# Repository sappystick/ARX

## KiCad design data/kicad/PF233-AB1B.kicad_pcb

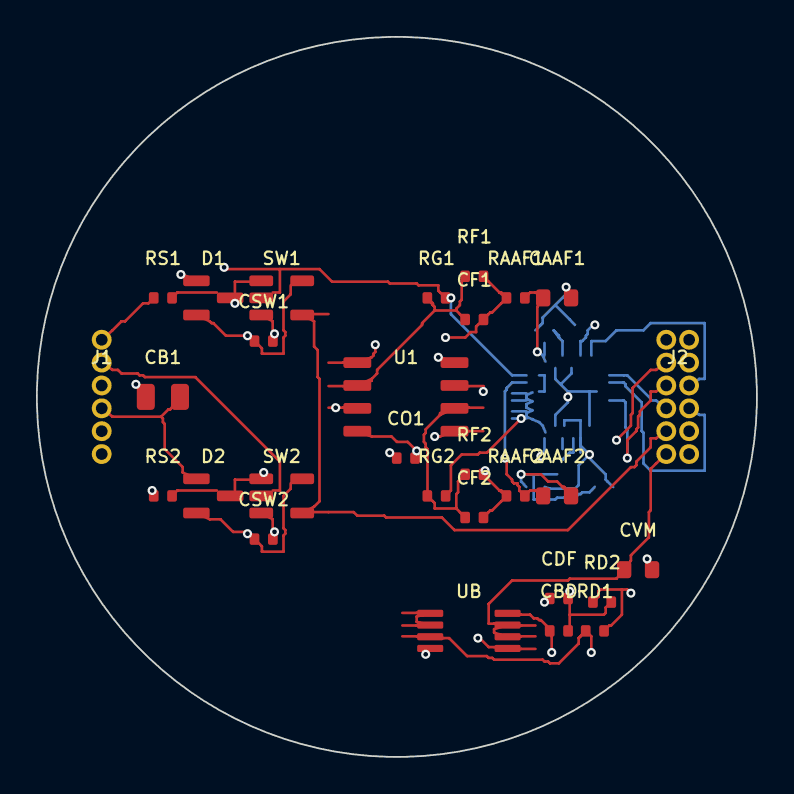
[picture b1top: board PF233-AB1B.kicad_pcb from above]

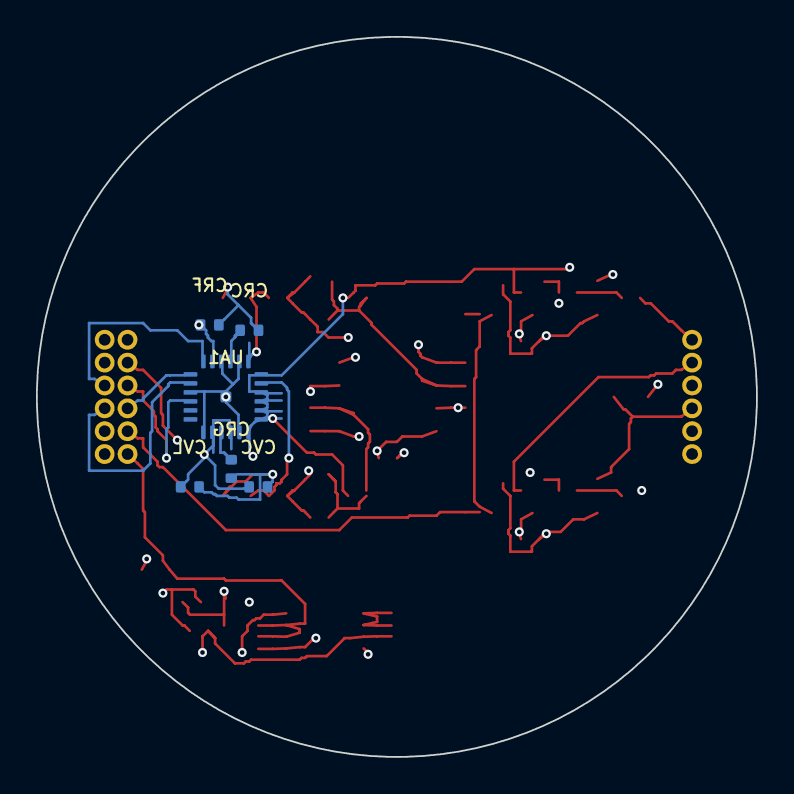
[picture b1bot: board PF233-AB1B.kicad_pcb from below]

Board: 6 copper layers, 40.0 x 40.0 mm, 35 parts (6 on the bottom side), 24 nets.

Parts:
CAAF1, CAAF2: 2n2; C_0603_1608Metric
CB1: 10u; C_0805_2012Metric
CBD: 100n; C_0402_1005Metric
CDF: 100n; C_0402_1005Metric
CF1, CF2: 22p; C_0402_1005Metric
CO1: 100n; C_0402_1005Metric
CRC: 100n; C_0402_1005Metric
CRF: 1u; C_0402_1005Metric
CRG: 1u; C_0402_1005Metric
CSW1, CSW2: 100n; C_0402_1005Metric
CVC: 1u; C_0402_1005Metric
CVL: 1u; C_0402_1005Metric
CVM: 1u; C_0603_1608Metric
D1, D2: BAV199; SOT-23
J1: Antenna harness 6p solder pads 1.27mm; PinHeader_1x6_P1.27mm
J2: Main-board 2x6 1.27mm header; PinHeader_2x6_P1.27mm
RAAF1, RAAF2: 200; R_0402_1005Metric
RD1, RD2: 100k; R_0402_1005Metric
RF1, RF2: 390; R_0402_1005Metric
RG1, RG2: 10; R_0402_1005Metric
RS1, RS2: 1000; R_0402_1005Metric
SW1, SW2: 74LVC1G66; SOT-23-5
U1: OPA2211; SOIC-8_3.9x4.9mm_P1.27mm
UA1: AD7389-4; CP-24-25_ADI_LFCSP-24-1EP_4x4mm_P0.5mm_EP0.61x0.61mm
UB: OPA2365; MSOP-8_3x3mm_P0.65mm

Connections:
+3V3D: CVC.1, CVL.1, J2.3, UA1.2, UA1.4
+5VA: CB1.1, CBD.1, CO1.1, CSW1.1, CSW2.1, D1.2, D2.2, J2.1, SW1.5, SW2.5, U1.8, UB.8
ADCIN_MONO: CAAF2.1, RAAF2.2, UA1.11
ADCIN_Y8: CAAF1.1, RAAF1.2, UA1.13
BLANK: J2.9, SW1.4, SW2.4
CS: J2.6, UA1.18
FB_MONO: CF2.1, RF2.1, RG2.1, U1.6
FB_Y8: CF1.1, RF1.1, RG1.1, U1.2
GND: CAAF1.2, CAAF2.2, CB1.2, CBD.2, CDF.2, CO1.2, CRC.2, CRF.2, CRG.2, CSW1.2, CSW2.2, CVC.2, CVL.2, CVM.2, D1.1, D2.1, J1.3, J1.4, J1.5, J1.6, J2.2, J2.4, J2.12, RD2.2, SW1.3, SW2.3, U1.4, UA1.1, UA1.5, UA1.14, UA1.16, UA1.21, UA1.25, UB.4
IN_MONO: D2.3, RS2.2, SW2.1, U1.5
IN_Y8: D1.3, RS1.2, SW1.1, U1.3
OUT_MONO: CF2.2, RAAF2.1, RF2.2, U1.7
OUT_Y8: CF1.2, RAAF1.1, RF1.2, U1.1
RAW_MONO: J2.10, RS2.1
RAW_Y8: J1.1, RS1.1
REFCAP: CRC.1, UA1.15
REGCAP: CRG.1, UA1.3
SCLK: J2.5, UA1.22
SDO1: J2.7, UA1.19
SDO2: J2.8, UA1.20
VCM: CVM.1, J1.2, J2.11, RG1.2, RG2.2, SW1.2, SW2.2, UA1.6, UA1.7, UA1.8, UA1.9, UA1.10, UA1.12, UB.6, UB.7
VCM_DIV: CDF.1, RD1.2, RD2.1, UB.5
VREF: UB.1, UB.2
VREF_RAW: CRF.1, RD1.1, UA1.17, UB.3

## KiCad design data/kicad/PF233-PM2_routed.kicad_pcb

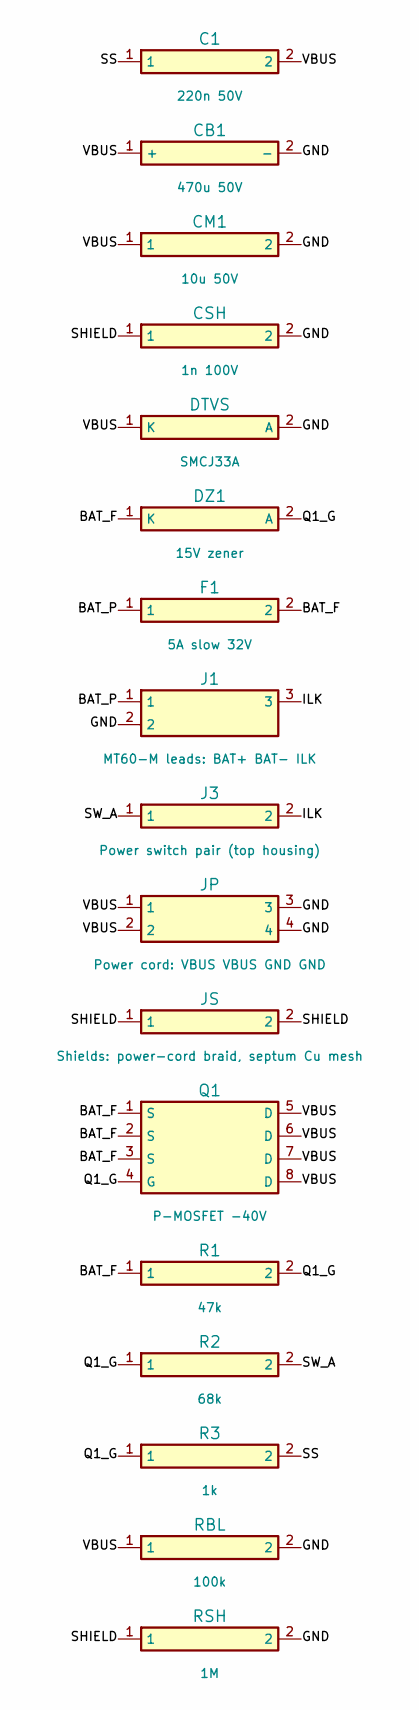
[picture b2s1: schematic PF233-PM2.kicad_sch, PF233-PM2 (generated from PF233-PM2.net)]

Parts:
C1: 220n 50V; C_0805_2012Metric
CB1: 470u 50V; CP_Elec_10x10
CM1: 10u 50V; C_1210_3225Metric
CSH: 1n 100V; C_0603_1608Metric
DTVS: SMCJ33A; D_SMC
DZ1: 15V zener; D_SOD-123
F1: 5A slow 32V; Fuse_1812_4532Metric
J1: MT60-M leads: BAT+ BAT- ILK; Wire_pads_1x3_P5.08mm
J3: Power switch pair (top housing); Wire_pads_1x2_P2.54mm
JP: Power cord: VBUS VBUS GND GND; Wire_pads_1x4_P5.08mm
JS: Shields: power-cord braid, septum Cu mesh; Wire_pads_1x2_P2.54mm
Q1: P-MOSFET -40V; SOIC-8_3.9x4.9mm_P1.27mm
R1: 47k; R_0603_1608Metric
R2: 68k; R_0603_1608Metric
R3: 1k; R_0603_1608Metric
RBL: 100k; R_1206_3216Metric
RSH: 1M; R_0603_1608Metric

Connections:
BAT_F: DZ1.1 (K), F1.2, Q1.1 (S), Q1.2 (S), Q1.3 (S), R1.1
BAT_P: F1.1, J1.1
GND: CB1.2 (-), CM1.2, CSH.2, DTVS.2 (A), J1.2, JP.3, JP.4, RBL.2, RSH.2; also elsewhere on the board
ILK: J1.3, J3.2
Q1_G: DZ1.2 (A), Q1.4 (G), R1.2, R2.1, R3.1
SHIELD: CSH.1, JS.1, JS.2, RSH.1
SS: C1.1, R3.2
SW_A: J3.1, R2.2
VBUS: C1.2, CB1.1 (+), CM1.1, DTVS.1 (K), JP.1, JP.2, Q1.5 (D), Q1.6 (D), Q1.7 (D), Q1.8 (D), RBL.1; also elsewhere on the board

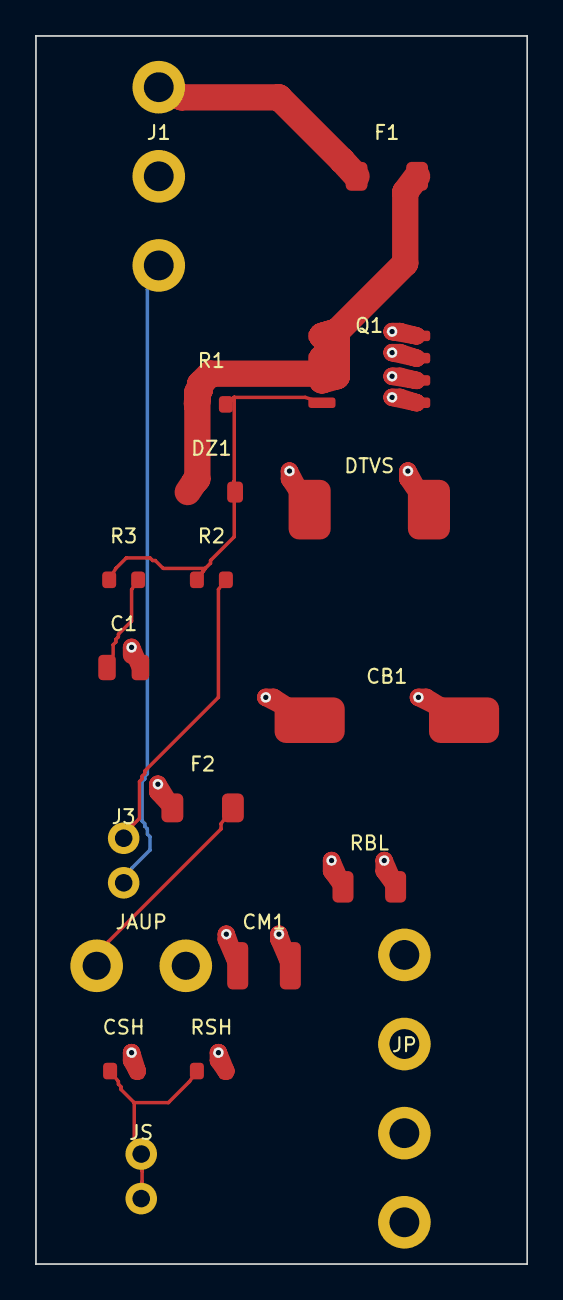
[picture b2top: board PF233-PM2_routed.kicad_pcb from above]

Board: 4 copper layers, 28.0 x 70.0 mm, 19 parts (0 on the bottom side), 10 nets.

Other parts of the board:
F2: 0.5A slow 32V; Fuse_1206_3216Metric
JAUP: Power to AU1: VBUS_AU, GND; SolderPad_2x_P5.08mm

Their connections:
GND: JAUP.2; also elsewhere on the board
VBUS: F2.1; also elsewhere on the board
VBUS_AU: F2.2, JAUP.1

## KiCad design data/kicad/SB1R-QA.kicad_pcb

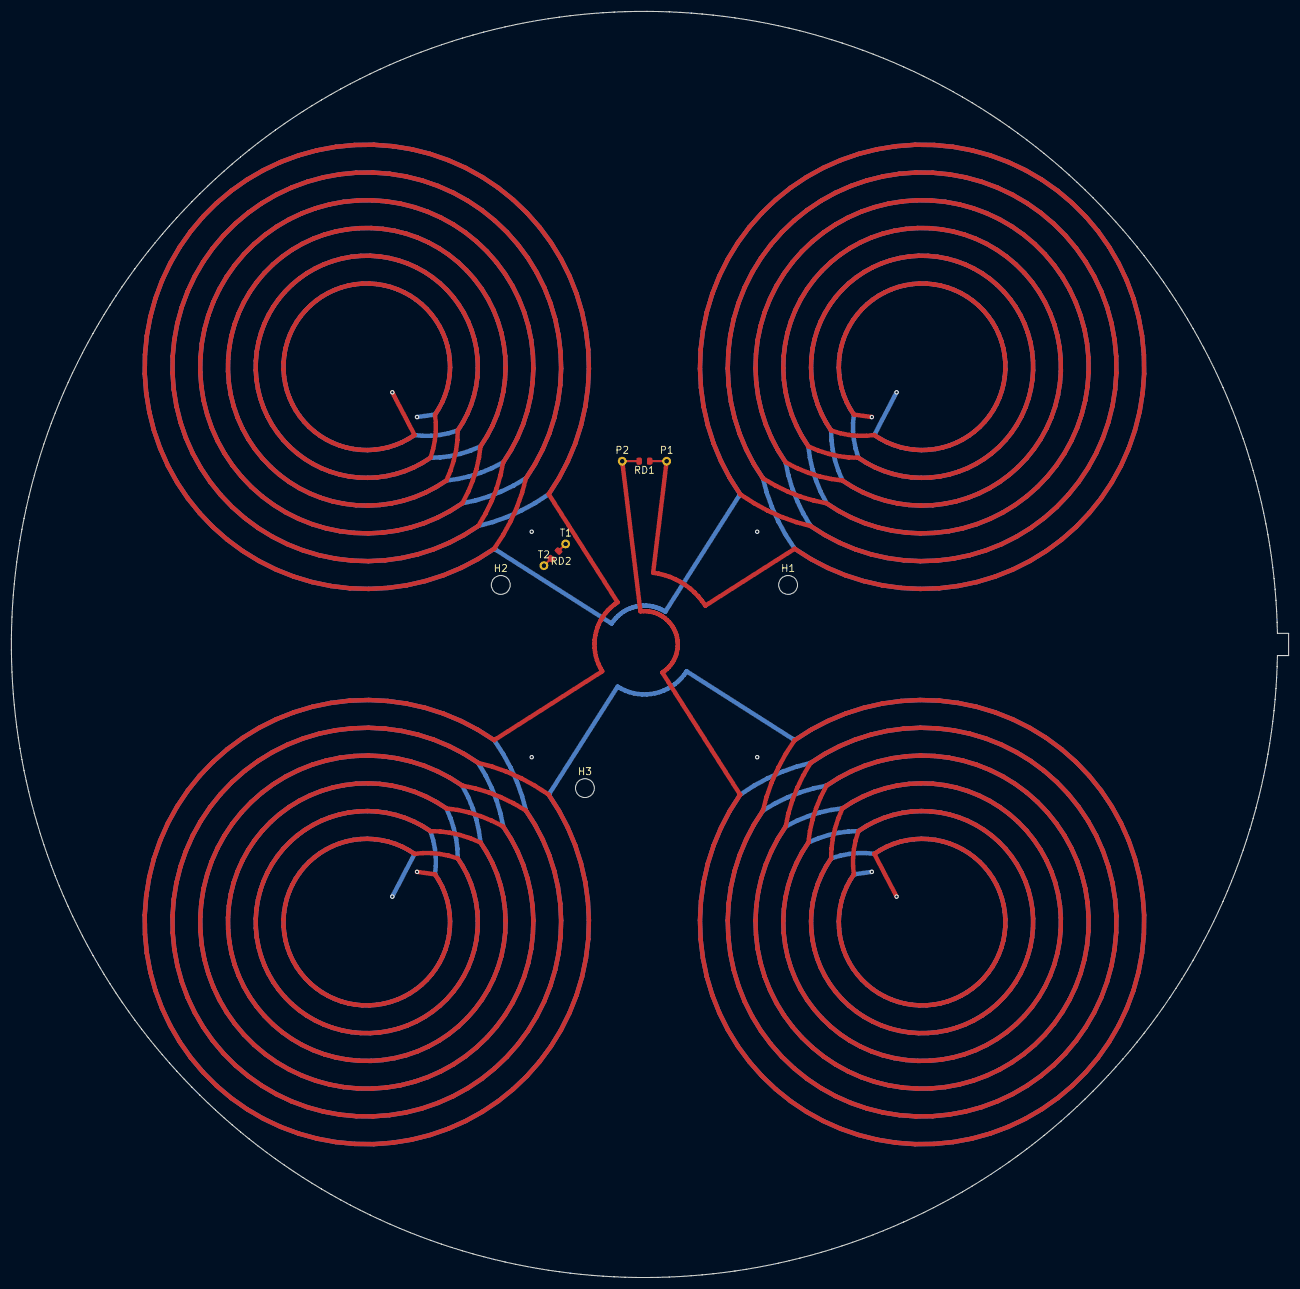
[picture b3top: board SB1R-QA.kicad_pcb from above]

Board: 4 copper layers, 230.0 x 228.0 mm, 9 parts (0 on the bottom side), 3 nets.

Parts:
H1, H2, H3: MH_M3
P1, P2: LEAD_PAD
RD1, RD2: 680R 0.1% thin film 0805, non-magnetic terminatio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; R_0805_2012Metric
T1, T2: TRANSFER_PAD

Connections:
QA_COIL: P1.1, P2.1, RD1.1, RD1.2
QB_T1: RD2.1, T1.1
QB_T2: RD2.2, T2.1

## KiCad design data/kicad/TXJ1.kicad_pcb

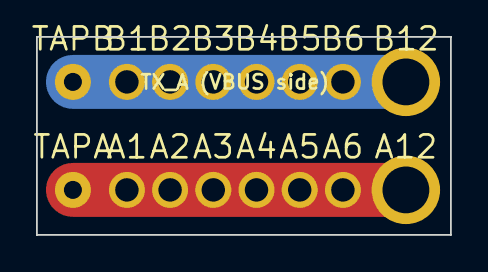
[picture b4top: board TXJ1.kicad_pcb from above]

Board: 2 copper layers, 23.0 x 11.0 mm, 16 parts (0 on the bottom side), 2 nets.

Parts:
A1, A2, A3, A4, A5, A6, A12: PTH
B1, B2, B3, B4, B5, B6, B12: PTH
TAPA: PTH
TAPB: PTH

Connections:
TX_A: A1.1, A2.1, A3.1, A4.1, A5.1, A6.1, A12.1, TAPA.1
TX_B: B1.1, B2.1, B3.1, B4.1, B5.1, B6.1, B12.1, TAPB.1

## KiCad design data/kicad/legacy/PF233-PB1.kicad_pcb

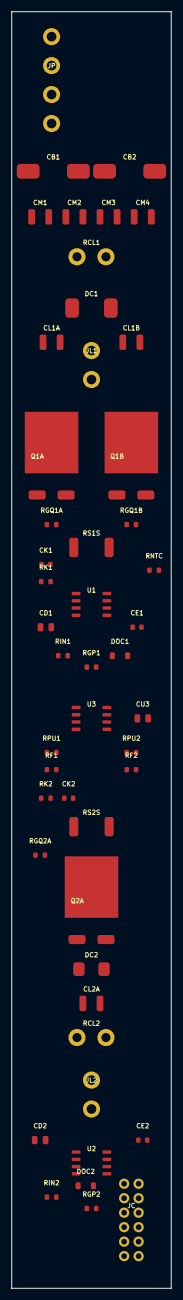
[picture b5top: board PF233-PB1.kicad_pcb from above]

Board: 4 copper layers, 28.0 x 224.0 mm, 48 parts (0 on the bottom side), 27 nets, no tracks yet.

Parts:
CB1, CB2: 470u 50V; CP_Elec_10x10
CD1, CD2: 1u 25V; C_0805_2012Metric
CE1, CE2: 100n; C_0603_1608Metric
CK1, CK2: 100p; C_0603_1608Metric
CL1A, CL1B: 100n 630V; C_1210_3225Metric
CL2A: 1u 100V; C_1210_3225Metric
CM1, CM2, CM3, CM4: 10u 50V; C_1210_3225Metric
CU3: 1u 25V; C_0805_2012Metric
DC1: ES3J 600V 3A; D_SMC
DC2: ES2D 200V 2A; D_SMB
DOC1, DOC2: BAS16; D_SOD-123
JC: Controller I/F; Pin_header_2x6_P2.54mm
JL1: Coil outer: DRAIN, VBUS; Terminal_block_1x2_P5.08mm
JL2: Coil inner: DRAIN, VBUS; Terminal_block_1x2_P5.08mm
JP: Power in: VBUS VBUS GND GND; Terminal_block_1x4_P5.08mm
Q1A, Q1B: 650V SJ 95mR; TO-263-3_TabPin2
Q2A: 100V 10mR; TO-263-3_TabPin2
RCL1: external 5k 10W; SolderPad_2x_P5.08mm
RCL2: external 100R 5W; SolderPad_2x_P5.08mm
RF1, RF2: 1k; R_0603_1608Metric
RGP1, RGP2: 10k; R_0603_1608Metric
RGQ1A, RGQ1B, RGQ2A: 10; R_0603_1608Metric
RIN1, RIN2: 100; R_0603_1608Metric
RK1, RK2: 100; R_0603_1608Metric
RNTC: 10k NTC; R_0603_1608Metric
RPU1, RPU2: 10k; R_0603_1608Metric
RS1S, RS2S: 10m 3W; R_2512_6332Metric
U1, U2: TC4420; SOIC-8_3.9x4.9mm_P1.27mm
U3: LM393; SOIC-8_3.9x4.9mm_P1.27mm

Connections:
AUX12: CD1.1, CD2.1, CE1.1, CE2.1, CU3.1, JC.1, RPU1.2, RPU2.2, U1.1, U1.8, U2.1, U2.8, U3.8
CLAMP1: CL1A.1, CL1B.1, DC1.1, RCL1.1
CLAMP2: CL2A.1, DC2.1, RCL2.1
DRAIN1: DC1.2, JL1.1, Q1A.2, Q1B.2
DRAIN2: DC2.2, JL2.1, Q2A.2
DRVIN1: DOC1.2, RIN1.2, U1.2
DRVIN2: DOC2.2, RIN2.2, U2.2
FAULT1_N: JC.7, RF1.2
FAULT2_N: JC.8, RF2.2
G1: RGP1.1, RGQ1A.1, RGQ1B.1, U1.6, U1.7
G2: RGP2.1, RGQ2A.1, U2.6, U2.7
GATE_Q1A: Q1A.1, RGQ1A.2
GATE_Q1B: Q1B.1, RGQ1B.2
GATE_Q2A: Q2A.1, RGQ2A.2
GND: CB1.2, CB2.2, CD1.2, CD2.2, CE1.2, CE2.2, CK1.2, CK2.2, CM1.2, CM2.2, CM3.2, CM4.2, CU3.2, JC.2, JC.12, JP.3, JP.4, RGP1.2, RGP2.2, RNTC.2, RS1S.2, RS2S.2, U1.4, U1.5, U2.4, U2.5, U3.4
ISENSE1: CK1.1, JC.9, RK1.2, U3.2
ISENSE2: CK2.1, JC.10, RK2.2, U3.6
NTC_SENSE: JC.11, RNTC.1
OC1_OUT: DOC1.1, RF1.1, RPU1.1, U3.1
OC2_OUT: DOC2.1, RF2.1, RPU2.1, U3.7
REF_I1: JC.5, U3.3
REF_I2: JC.6, U3.5
SRC1: Q1A.3, Q1B.3, RK1.1, RS1S.1
SRC2: Q2A.3, RK2.1, RS2S.1
TX1_IN: JC.3, RIN1.1
TX2_IN: JC.4, RIN2.1
VBUS: CB1.1, CB2.1, CL1A.2, CL1B.2, CL2A.2, CM1.1, CM2.1, CM3.1, CM4.1, JL1.2, JL2.2, JP.1, JP.2, RCL1.2, RCL2.2

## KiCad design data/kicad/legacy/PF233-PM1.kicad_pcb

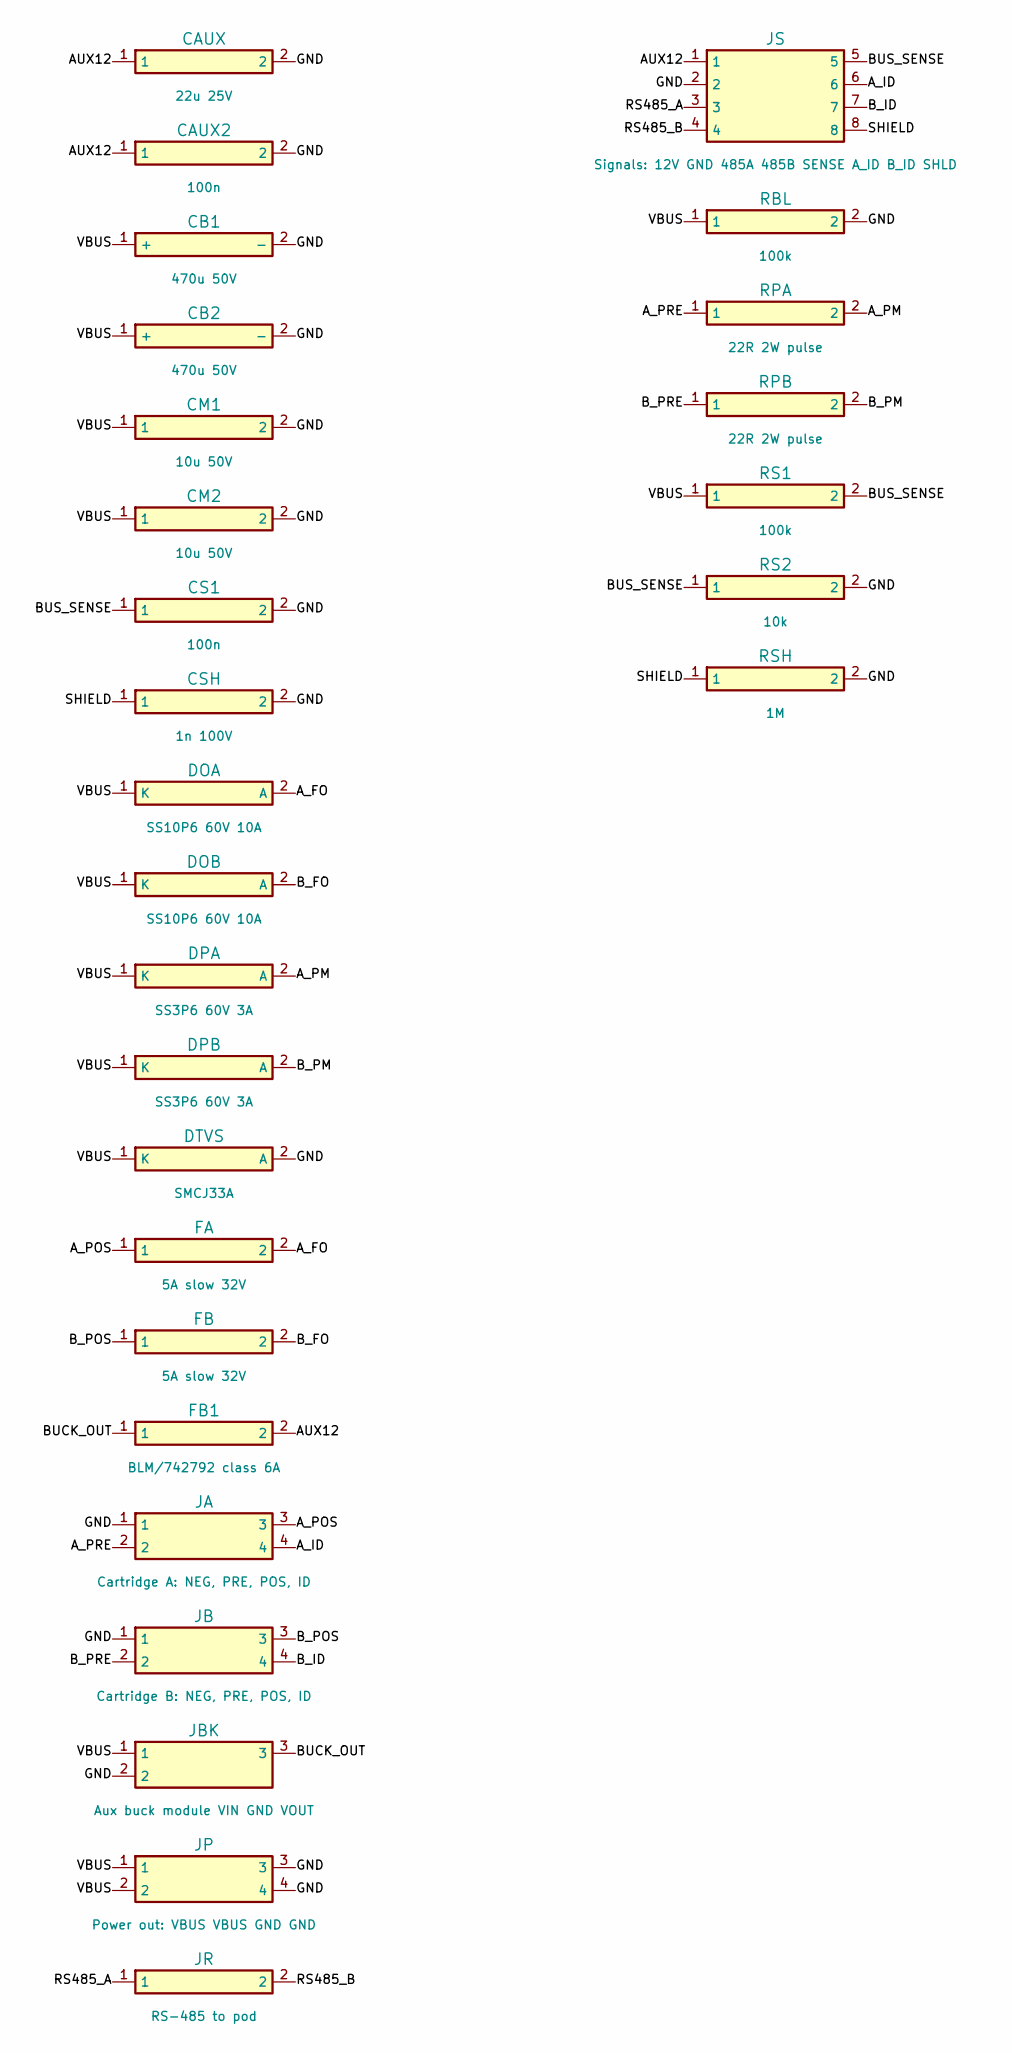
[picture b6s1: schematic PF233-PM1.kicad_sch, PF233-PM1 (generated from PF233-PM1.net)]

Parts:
CAUX: 22u 25V; C_1210_3225Metric
CAUX2: 100n; C_0603_1608Metric
CB1, CB2: 470u 50V; CP_Elec_10x10
CM1, CM2: 10u 50V; C_1210_3225Metric
CS1: 100n; C_0603_1608Metric
CSH: 1n 100V; C_0603_1608Metric
DOA: SS10P6 60V 10A; D_SMC
DOB: SS10P6 60V 10A; D_SMC
DPA: SS3P6 60V 3A; D_SMB
DPB: SS3P6 60V 3A; D_SMB
DTVS: SMCJ33A; D_SMC
FA: 5A slow 32V; Fuse_1812_4532Metric
FB: 5A slow 32V; Fuse_1812_4532Metric
FB1: BLM/742792 class 6A; L_1812_4532Metric
JA: Cartridge A: NEG, PRE, POS, ID; Terminal_block_1x4_P5.08mm
JB: Cartridge B: NEG, PRE, POS, ID; Terminal_block_1x4_P5.08mm
JBK: Aux buck module VIN GND VOUT; Pin_header_1x3_P2.54mm
JP: Power out: VBUS VBUS GND GND; Terminal_block_1x4_P5.08mm
JR: RS-485 to pod; Pin_header_1x2_P2.54mm
JS: Signals: 12V GND 485A 485B SENSE A_ID B_ID SHLD; Pin_header_2x4_P2.54mm
RBL: 100k; R_1206_3216Metric
RPA: 22R 2W pulse; R_2512_6332Metric
RPB: 22R 2W pulse; R_2512_6332Metric
RS1: 100k; R_0603_1608Metric
RS2: 10k; R_0603_1608Metric
RSH: 1M; R_0603_1608Metric

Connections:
AUX12: CAUX.1, CAUX2.1, FB1.2, JS.1
A_FO: DOA.2 (A), FA.2
A_ID: JA.4, JS.6
A_PM: DPA.2 (A), RPA.2
A_POS: FA.1, JA.3
A_PRE: JA.2, RPA.1
BUCK_OUT: FB1.1, JBK.3
BUS_SENSE: CS1.1, JS.5, RS1.2, RS2.1
B_FO: DOB.2 (A), FB.2
B_ID: JB.4, JS.7
B_PM: DPB.2 (A), RPB.2
B_POS: FB.1, JB.3
B_PRE: JB.2, RPB.1
GND: CAUX.2, CAUX2.2, CB1.2 (-), CB2.2 (-), CM1.2, CM2.2, CS1.2, CSH.2, DTVS.2 (A), JA.1, JB.1, JBK.2, JP.3, JP.4, JS.2, RBL.2, RS2.2, RSH.2
RS485_A: JR.1, JS.3
RS485_B: JR.2, JS.4
SHIELD: CSH.1, JS.8, RSH.1
VBUS: CB1.1 (+), CB2.1 (+), CM1.1, CM2.1, DOA.1 (K), DOB.1 (K), DPA.1 (K), DPB.1 (K), DTVS.1 (K), JBK.1, JP.1, JP.2, RBL.1, RS1.1

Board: 4 copper layers, 28 parts (0 on the bottom side), 18 nets, no tracks yet.
